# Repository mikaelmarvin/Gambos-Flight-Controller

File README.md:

# Gambos flight controller

Custom **STM32F446** flight-controller PCB and firmware — schematic through layout, manufacture, assembly, bring-up, application and driver development.

## At a glance

|               |                                                                        |
| ---------------| ------------------------------------------------------------------------|
| **MCU**       | STM32F446RET6 (Cortex-M4 + FPU)                                        |
| **Sensors**   | Accelerometer, gyroscope, magnetometer, barometer, temperature         |
| **Storage**   | External flash + microSD                                               |
| **Actuation** | 5× hobby servo PWM, ESC motor PWM                                      |
| **Wireless**  | nRF24L01+ telemetry / command link                                     |
| **Debug**     | SWD + UART (SEGGER J-Link)                                             |
| **PCB**       | 4-layer, 75 × 50 mm — KiCad, manufactured **v1.0**                     |
| **Firmware**  | CMake, FreeRTOS — `gambos` target                                  |
| **Status**    | v1.0 built; hardware bring-up in progress; flight software in progress |
| **Schematic** | [Gambos PCB schematic (PDF)](https://github.com/mikaelmarvin/gambos_hardware/blob/main/docs/gambos-pcb.pdf) — KiCad export, v1.0 |

## Schematic (v1.0)

The full board schematic is published as a PDF:

**[Gambos PCB schematic (PDF)](https://github.com/mikaelmarvin/gambos_hardware/blob/main/docs/gambos-pcb.pdf)**

The KiCad design, the schematic PDF and the hardware documentation live in a separate repository, [gambos_hardware](https://github.com/mikaelmarvin/gambos_hardware).

## Render and Bring-up setup

<p align="center">
  <table cellspacing="0" cellpadding="12">
    <tr>
      <td align="center" valign="top">
        
        <br>
        <sub>3D PCB render</sub>
      </td>
      <td align="center" valign="top">
        
        <br>
        <sub>Testing the power section on the bench</sub>
      </td>
    </tr>
  </table>
</p>

Render of v1.0 layout in KiCad (left) and early bench bring-up (right), started with the power section before moving to testing other peripherals.

## Hardware block diagram

<p align="center">
  
  <br>
  <sub>Hardware block diagram</sub>
</p>

Buses, actuation, and interfaces are described in [Hardware architecture](https://github.com/mikaelmarvin/gambos_hardware/blob/main/docs/hardware-architecture.md).

## Software architecture

*(diagram pending)* — layer stack, drivers, RTOS tasks, and flight logic are described in [Software architecture](docs/software/software-architecture.md).

## Documentation

Full index: **[docs/index.md](docs/index.md)**

**Hardware:** documentation for the v1.0 board lives in [gambos_hardware](https://github.com/mikaelmarvin/gambos_hardware#documentation-v10) — architecture, physical design, power, storage, sensing, user interface, and the hardware roadmap.

**Software:** [docs/software/software-architecture.md](docs/software/software-architecture.md) → [project/README.md](project/README.md) · [Firmware roadmap](docs/software/roadmap.md)

## Repository layout

| Directory                | Purpose                                         |
| ------------------------ | ----------------------------------------------- |
| `[project/](project/)`   | STM32 firmware (CMake, FreeRTOS)                |
| `[docs/](docs/)`         | Software documentation, figures                 |

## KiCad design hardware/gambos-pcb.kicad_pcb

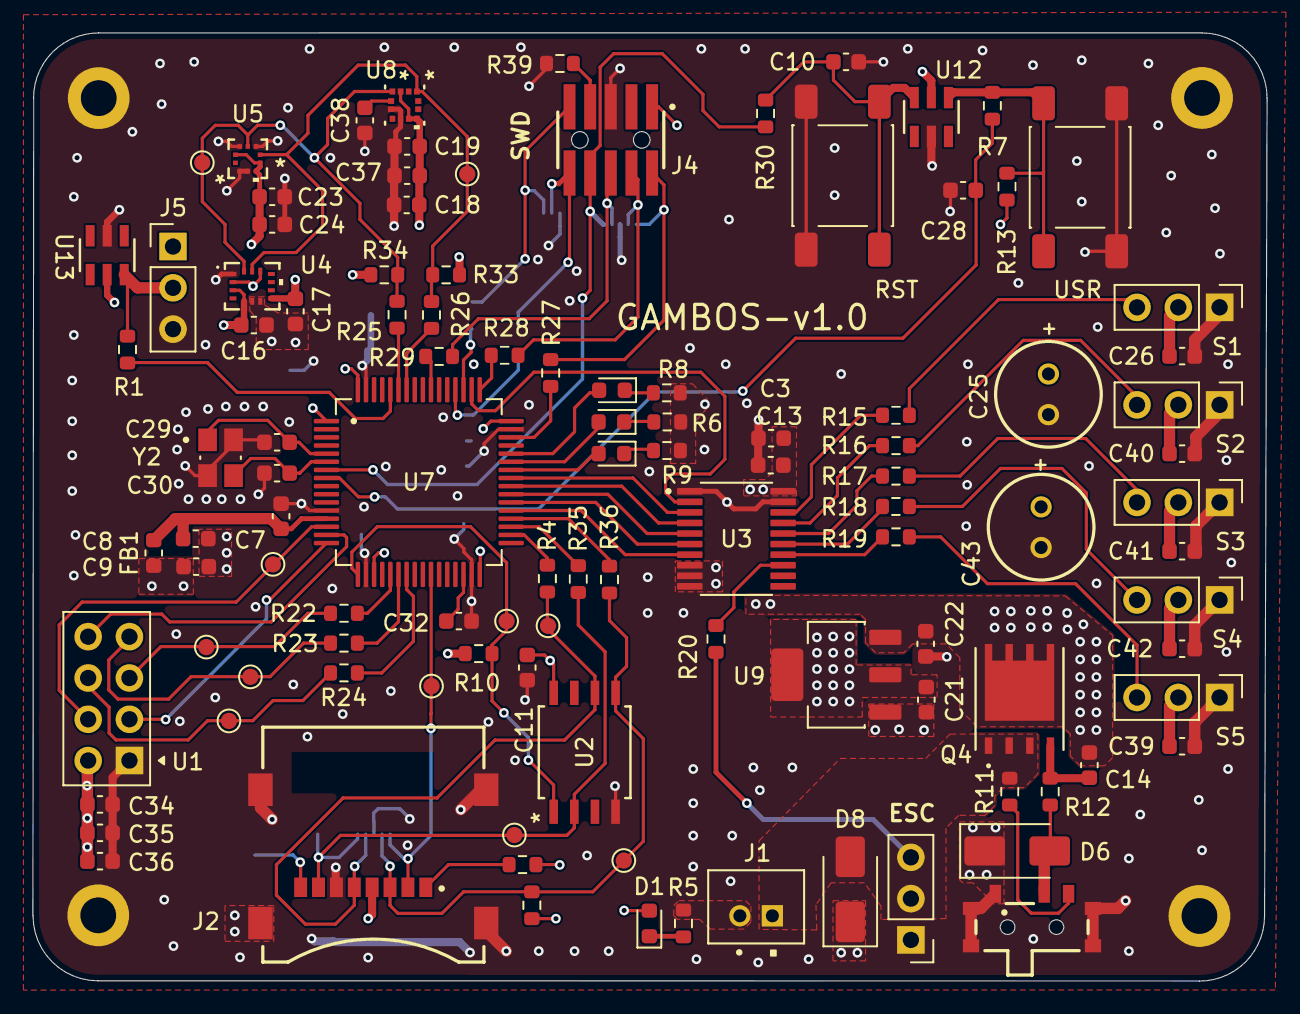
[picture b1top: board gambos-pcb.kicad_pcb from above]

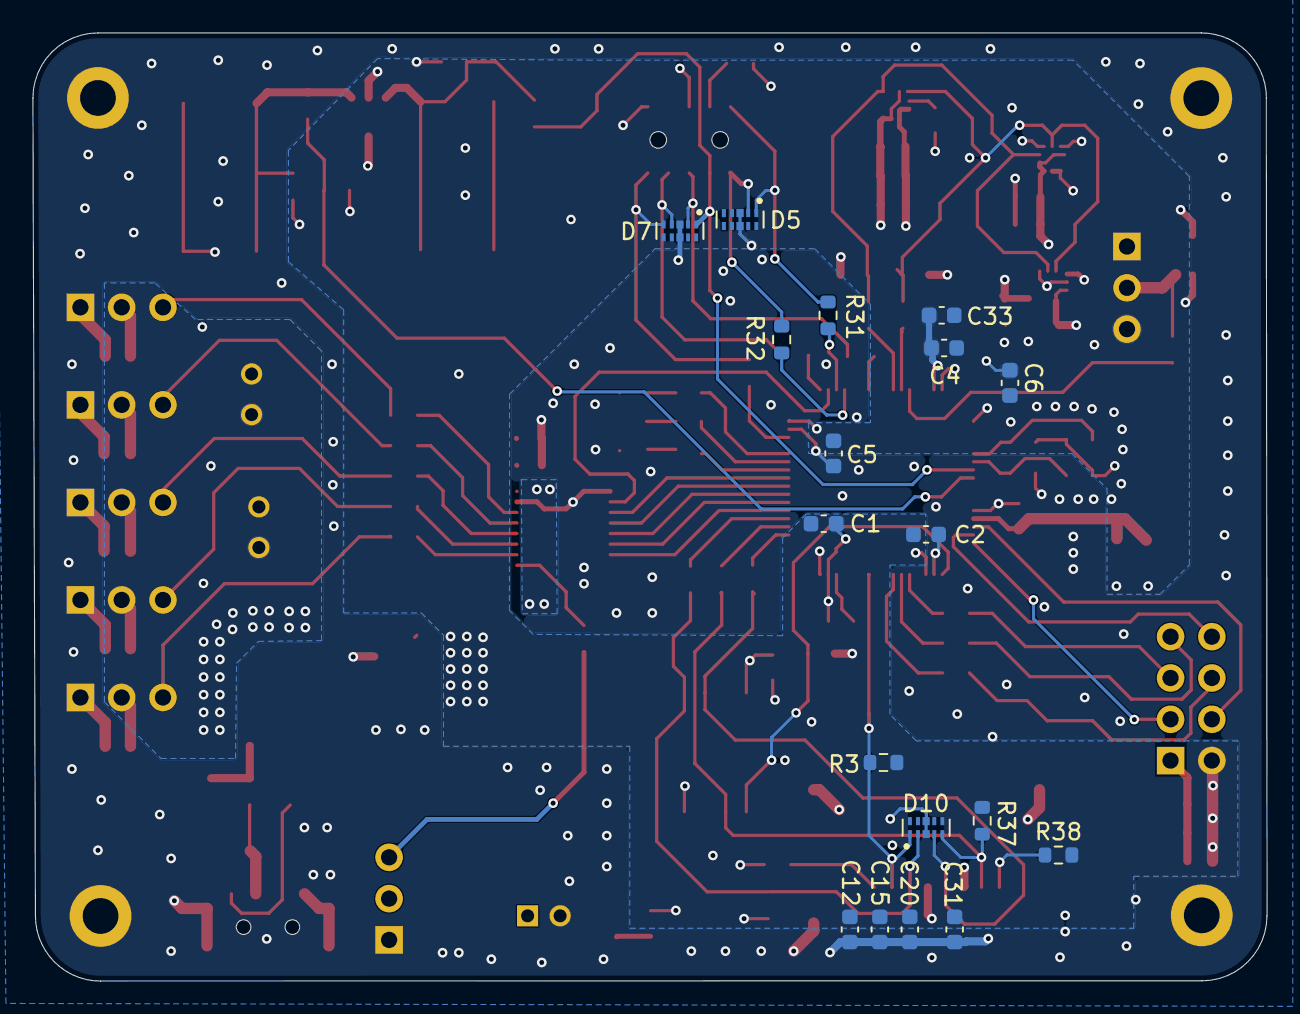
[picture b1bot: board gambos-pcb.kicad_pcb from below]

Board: 4 copper layers, 75.9 x 58.3 mm, 130 parts (18 on the bottom side), 77 nets.

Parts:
C1, C2, C4, C5, C10, C11, C13, C14, C16, C17, C19, C23, C24, C28, C31, C33, C35, C37: 100n; C_0603_1608Metric
C3, C8, C9, C20, C22: 1u; C_0603_1608Metric
C6, C15, C18, C26, C36, C39, C40, C41, C42: 10u; C_0603_1608Metric
C7, C34: 10n; C_0603_1608Metric
C12: 22u; C_0603_1608Metric
C21, C32: 4u7; C_0603_1608Metric
C25, C43: 470u; WCAP-ATG8_6.3X11_DXL_
C29, C30: 8p; C_0603_1608Metric
C38: 220n; C_0603_1608Metric
D1: LED0; LED_0603_1608Metric
D2: LED1; LED_0603_1608Metric
D3: LED2; LED_0603_1608Metric
D4: LED3; LED_0603_1608Metric
D5, D7, D10: ESD8104MUTAG; DIO_ESD8104MUTAG
D6, D8: SMAJ5.0CA; D_SMA
FB1: 120R; L_0603_1608Metric
H1, H2, H3, H4: MountingHole_Pad; MountingHole_2.2mm_M2_DIN965_Pad
J1: JST-PH
J2: Micro_SD_Card; GCT_MEM2067-02-180-00-A_REVB
J4: FTSH-105-01-F-DV-K-A; SAMTEC_FTSH-105-01-F-DV-K-A
J5, J7, J9, J10, J11, J12, J13: Conn_01x03_Pin; PinHeader_1x03_P2.54mm_Vertical
Q4: DMP3010LPSQ-13
R1, R10, R12, R13: 10k; R_0603_1608Metric
R2, R3, R7, R21, R37, R38: 47k; R_0603_1608Metric
R4, R15, R16, R17, R18, R19, R20, R22, R23, R24, R25, R26, R27, R28, R29, R31, R32, R35, R36: 0R; R_0603_1608Metric
R5, R6, R8, R9: 260R; R_0603_1608Metric
R11: 100k; R_0603_1608Metric
R30: 470R; R_0603_1608Metric
R33, R34: 4k7; R_0603_1608Metric
R39: 100R; R_0603_1608Metric
SW1, SW3: SW_Push; SW_Push_1P1T_NO_E-Switch_TL3301NxxxxxG
Slide_SW1: 450404015514
TP2, TP3, TP4, TP5, TP6, TP7, TP8, TP9, TP12, TP13, TP14: TestPoint; TestPoint_Pad_D1.0mm
U1: NRF24L01_Breakout; nRF24L01_Breakout
U2: AT25SF128A-SHB-T; IC8_AT25SF128A-SHB-T_ADO
U3: SN74AHCT541PWR; SOP65P640X120-20N
U4: LSM6DSVTR
U5: BMP384; LGA10_2.0X2.0X0.95_BOS
U7: STM32F446RET6
U8: IIS2MDCTR; LGA-12_2X2X0P7_STM
U9: LDL1117S33R
U12, U13: CM1293A-04SO; SC74-6_3P1X1P7_ONS
Y2: TSX-3225_26MHZ; XTAL_TSX-3225_26.0000MF09Z-AC0

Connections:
+3.3VA: C7.1, C8.1, FB1.1, U7.13 (VDDA)
+3V3: C1.1, C2.1, C4.1, C5.1, C6.1, C9.1, C11.1, C12.2, C15.2, C16.1, C17.1, C18.1, C19.1, C20.2, C21.1, C23.1, C24.2, C31.2, C33.1, C34.1, C35.1, C36.1, C37.1, D1.2 (A), FB1.2, J2.4 (VDD), J4.01, J5.1, R2.1, R3.1, R10.1, R13.2, R21.1, R33.1, R34.1, R37.1, R38.2, U1.2 (VCC), U2.8 (VCC), U4.2 (SDX), U4.3 (SCX), U4.5 (VDD_IO), U4.8 (VDD), U4.12 (CS), U5.1 (VDDIO), U5.6 (CSB), U5.10 (VDD), U7.1 (VBAT), U7.19 (VDD), U7.32 (VDD), U7.48 (VDD), U7.64 (VDD), U8.3 (CS), U8.9 (VDD), U8.10 (VDD_IO), U9.2 (VOUT_2), U9.4 (VOUT_1), U12.5 (VP), U13.5 (VP)
+5V: C3.1, C13.1, C14.1, C22.1, C25.1, C26.1, C39.1, C40.1, C41.1, C42.1, C43.1, J7.2, J9.2, J10.2, J11.2, J12.2, Q4.5 (D), Q4.6 (D), Q4.7 (D), Q4.8 (D), U3.20 (VCC), U9.3 (VIN)
/Schematic/I2C.SCL: R26.2, R33.2, TP12.1 (1_1), U4.13 (SCL), U5.2 (SCK), U8.1 (SCL/SPC)
/Schematic/I2C.SDA: R25.2, R34.2, TP13.1 (1_1), U4.14 (SDA), U5.4 (SDI), U8.4 (SDA/SDI/SDO)
/Schematic/Microcontroller/BOOT0: R1.2, U7.60 (BOOT0)
/Schematic/Microcontroller/BOOT0_ESD: J5.2, R1.1, U13.6 (CH4)
/Schematic/Microcontroller/HSE_IN: C29.2, U7.5 (PH0), Y2.1
/Schematic/Microcontroller/HSE_OUT: C30.1, U7.6 (PH1), Y2.3
/Schematic/Microcontroller/NRST_ESD: C10.1, R30.1, SW3.2, U12.6 (CH4)
/Schematic/Microcontroller/PWMs.ESC_IN: U3.7 (A6), U7.37 (PC6)
/Schematic/Microcontroller/PWMs.SERVO1_IN: U3.2 (A1), U7.50 (PA15)
/Schematic/Microcontroller/PWMs.SERVO2_IN: U3.3 (A2), U7.41 (PA8)
/Schematic/Microcontroller/PWMs.SERVO3_IN: U3.4 (A3), U7.40 (PC9)
/Schematic/Microcontroller/PWMs.SERVO4_IN: U3.5 (A4), U7.39 (PC8)
/Schematic/Microcontroller/PWMs.SERVO5_IN: U3.6 (A5), U7.38 (PC7)
/Schematic/Microcontroller/USER_BTN: C28.1, R7.2, U7.8 (PC0)
/Schematic/Microcontroller/USER_BTN_ESD: R7.1, R13.1, SW1.2, U12.4 (CH3)
/Schematic/Microcontroller/USER_LED1: D2.2 (A), U7.44 (PA11)
/Schematic/Microcontroller/USER_LED2: D3.2 (A), U7.43 (PA10)
/Schematic/Microcontroller/USER_LED3: D4.2 (A), U7.42 (PA9)
/Schematic/Power and ESC/GATE: C14.2, Q4.4 (G), R12.2
/Schematic/Power and ESC/GATE_CTRL: D6.2 (A2), R12.1, Slide_SW1.2
/Schematic/Power and ESC/OFF: R11.2, Slide_SW1.3
/Schematic/Power and ESC/V_IN: D8.2 (A2), J1.1 (V_BAT), J13.2, Q4.1 (S), Q4.2 (S), Q4.3 (S), R11.1
/Schematic/SPI1.MISO_1: R23.2, TP4.1 (1_1), U1.7 (MISO)
/Schematic/SPI1.MOSI_1: R24.2, TP5.1 (1_1), U1.6 (MOSI)
/Schematic/SPI1.SCK_1: R22.2, TP3.1 (1_1), U1.5 (SCK)
/Schematic/SPI2.MISO_2: D10.5, J2.7 (DAT0), R35.2, R37.2, TP7.1 (1_1), U2.2 (SO(I/O1))
/Schematic/SPI2.MOSI_2: D10.2, J2.3 (CMD), R2.2, R36.2, TP14.1 (1_1), U2.5 (SI(I/O0))
/Schematic/SPI2.SCK_2: D10.4, J2.5 (CLK), R4.2, TP6.1 (1_1), U2.6 (SCK)
/Schematic/Servos and connectors/ESC_OUT: J13.3, R20.2
/Schematic/Servos and connectors/PWM1_1_5V: R16.1, U3.17 (Y2)
/Schematic/Servos and connectors/PWM2_1_5V: R15.1, U3.18 (Y1)
/Schematic/Servos and connectors/PWM3_1_5V: R19.1, U3.14 (Y5)
/Schematic/Servos and connectors/PWM3_2_5V: R20.1, U3.13 (Y6)
/Schematic/Servos and connectors/PWM3_3_5V: R18.1, U3.15 (Y4)
/Schematic/Servos and connectors/PWM3_4_5V: R17.1, U3.16 (Y3)
/Schematic/Servos and connectors/SERVO1_OUT: J10.3, R15.2
/Schematic/Servos and connectors/SERVO2_OUT: J7.3, R16.2
/Schematic/Servos and connectors/SERVO3_OUT: J9.3, R17.2
/Schematic/Servos and connectors/SERVO4_OUT: J11.3, R18.2
/Schematic/Servos and connectors/SERVO5_OUT: J12.3, R19.2
FLASH_CS: R10.2, TP9.1 (1_1), U2.1 (*CS), U7.17 (PA3)
GND: C1.2, C2.2, C3.2, C4.2, C5.2, C6.2, C7.2, C8.2, C9.2, C10.2, C11.2, C12.1, C13.2, C15.1, C16.2, C17.2, C18.2, C19.2, C20.1, C21.2, C22.2, C23.2, C24.1, C25.2, C26.2, C28.2, C29.1, C30.2, C31.1, C32.2, C33.2, C34.2, C35.2, C36.2, C37.2, C38.2, C39.2, C40.2, C41.2, C42.2, C43.2, D5.3 (GND), D5.8 (GND), D6.1 (A1), D7.3 (GND), D7.8 (GND), D8.1 (A1), D10.3 (GND), D10.8 (GND), H1.1 (1_1), H2.1 (1_1), H3.1 (1_1), H4.1 (1_1), J1.2 (GND), J2.6 (VSS), J2.9, J2.10, J2.11, J2.12, J4.05, J5.3, J7.1, J9.1, J10.1, J11.1, J12.1, J13.1, R5.2, R6.1, R8.1, R9.1, R39.1, SW1.1, SW3.1, Slide_SW1.1, Slide_SW1.Z1, Slide_SW1.Z2, Slide_SW1.Z3, Slide_SW1.Z4, U1.1 (GND), U2.4 (GND), U3.1 (~OE1), U3.8 (A7), U3.9 (A8), U3.10 (GND), U3.19 (~OE2), U4.1 (SDO/SA0), U4.6 (GND), U4.7 (GND), U5.3 (VSS), U5.5 (SDO), U5.8 (VSS), U5.9 (VSS), U7.12 (VSSA), U7.18 (VSS), U7.31 (VSS), U7.47 (VSS), U7.63 (VSS), U8.6 (GND), U8.8 (GND), U9.1 (GND), U12.2 (VN), U13.2 (VN), Y2.2 (GND), Y2.4 (GND)
IRQ_SLD: U1.8 (IRQ), U7.15 (PA1)
NRF24_CE_SLD: U1.3 (CE), U7.16 (PA2)
NRF24_CS_SLD: TP2.1 (1_1), U1.4 (~CSN), U7.14 (PA0)
NRST: D7.1, J4.08, R30.2, U7.7 (NRST)
unnamed: D1.1 (K), R5.1
unnamed: D2.1 (K), R8.2
unnamed: D3.1 (K), R6.2
unnamed: D4.1 (K), R9.2
unnamed: J2.8 (DAT1), R38.1
unnamed: J2.1 (DAT2), R21.2
unnamed: J4.07, R39.2
unnamed: R22.1, U7.21 (PA5)
unnamed: R23.1, U7.22 (PA6)
unnamed: R24.1, U7.23 (PA7)
unnamed: R27.1, U7.46 (PA13)
unnamed: R28.1, U7.49 (PA14)
unnamed: R29.1, U7.55 (PB3)
unnamed: R26.1, U7.58 (PB6)
unnamed: R25.1, U7.59 (PB7)
unnamed: R4.1, U7.34 (PB13)
unnamed: R35.1, U7.35 (PB14)
unnamed: R36.1, U7.36 (PB15)
unnamed: R31.2, U7.51 (PC10)
unnamed: R32.2, U7.52 (PC11)
unnamed: C32.1, U7.30 (VCAP_1)
unnamed: C38.1, U8.5 (C1)
SD_CS: D10.1, J2.2 (DAT3/CD), R3.2, TP8.1 (1_1), U7.26 (PB0)
SWCLK: D7.4, J4.04, R28.2
SWDIO: D7.5, J4.02, R27.2
SWO: D7.2, J4.06, R29.2
UART4_RX: D5.2, J4.10, R32.1
UART4_TX: D5.1, J4.09, R31.1

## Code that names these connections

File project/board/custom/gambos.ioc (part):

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Mcu.Name=STM32F446R(C-E)Tx
Mcu.Package=LQFP64
Mcu.UserName=STM32F446RETx
PA0-WKUP.GPIOParameters=GPIO_Label
PA0-WKUP.GPIO_Label=RF_IRQ
PA0-WKUP.Signal=GPXTI0
PA1.GPIOParameters=GPIO_Label
PA1.GPIO_Label=RF_CS
PA1.Signal=GPIO_Output
PA10.GPIOParameters=GPIO_Label
PA10.GPIO_Label=LED2
PA10.Signal=GPIO_Output
PA11.GPIOParameters=GPIO_Label
PA11.GPIO_Label=LED1
PA11.Signal=GPIO_Output
PA12.GPIOParameters=GPIO_Label
PA12.GPIO_Label=BUFF_EN
PA12.Signal=GPIO_Output
PA13.Mode=Trace_Asynchronous_SW
PA13.Signal=SYS_JTMS-SWDIO
PA14.Mode=Trace_Asynchronous_SW
PA14.Signal=SYS_JTCK-SWCLK
PA15.GPIOParameters=GPIO_Label
PA15.GPIO_Label=SERVO1
PA15.Signal=S_TIM2_CH1_ETR
PA2.GPIOParameters=GPIO_Label
PA2.GPIO_Label=RF_CE
PA2.Signal=GPXTI2
PA3.GPIOParameters=GPIO_Label
PA3.GPIO_Label=FLASH_CS
PA3.Signal=GPIO_Output
PA5.Mode=Full_Duplex_Master
PA5.Signal=SPI1_SCK
PA6.Mode=Full_Duplex_Master
PA6.Signal=SPI1_MISO
PA7.Mode=Full_Duplex_Master
PA7.Signal=SPI1_MOSI
PA8.GPIOParameters=GPIO_Label
PA8.GPIO_Label=SERVO2
PA8.Signal=S_TIM1_CH1
PA9.GPIOParameters=GPIO_Label
PA9.GPIO_Label=LED3
PA9.Signal=GPIO_Output
PB13.Mode=Full_Duplex_Master
PB13.Signal=SPI2_SCK
PB14.Mode=Full_Duplex_Master
PB14.Signal=SPI2_MISO
PB15.Mode=Full_Duplex_Master
PB15.Signal=SPI2_MOSI
PB3.Mode=Trace_Asynchronous_SW
PB3.Signal=SYS_JTDO-SWO
PB6.Mode=I2C
PB6.Signal=I2C1_SCL
PB7.Mode=I2C
PB7.Signal=I2C1_SDA
PC0.GPIOParameters=GPIO_Label
PC0.GPIO_Label=USER_BTN
PC0.Signal=GPIO_Input
PC10.Mode=Asynchronous
PC10.Signal=UART4_TX
PC11.Mode=Asynchronous
PC11.Signal=UART4_RX
PC6.GPIOParameters=GPIO_Label
PC6.GPIO_Label=ESC
PC6.Signal=S_TIM3_CH1
PC7.GPIOParameters=GPIO_Label
PC7.GPIO_Label=SERVO5
PC7.Signal=S_TIM3_CH2
PC8.GPIOParameters=GPIO_Label
PC8.GPIO_Label=SERVO4
PC8.Signal=S_TIM3_CH3
PC9.GPIOParameters=GPIO_Label
PC9.GPIO_Label=SERVO3
PC9.Signal=S_TIM3_CH4
PH0-OSC_IN.Mode=HSE-External-Oscillator
PH0-OSC_IN.Signal=RCC_OSC_IN
PH1-OSC_OUT.Mode=HSE-External-Oscillator
PH1-OSC_OUT.Signal=RCC_OSC_OUT
RCC.HSE_VALUE=26000000
RCC.SYSCLKFreq_VALUE=180000000
RCC.SYSCLKSource=RCC_SYSCLKSOURCE_PLLCLK
board=custom

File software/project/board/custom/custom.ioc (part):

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Mcu.Name=STM32F446R(C-E)Tx
Mcu.Package=LQFP64
Mcu.UserName=STM32F446RETx
PA0-WKUP.GPIOParameters=GPIO_Label
PA0-WKUP.GPIO_Label=NRF24_CS
PA0-WKUP.Signal=GPIO_Output
PA1.GPIOParameters=GPIO_Label
PA1.GPIO_Label=IRQ
PA1.Signal=GPXTI1
PA10.GPIOParameters=GPIO_Label
PA10.GPIO_Label=LED2
PA10.Signal=GPIO_Output
PA11.GPIOParameters=GPIO_Label
PA11.GPIO_Label=LED1
PA11.Signal=GPIO_Output
PA13.Mode=Trace_Asynchronous_SW
PA13.Signal=SYS_JTMS-SWDIO
PA14.Mode=Trace_Asynchronous_SW
PA14.Signal=SYS_JTCK-SWCLK
PA15.GPIOParameters=GPIO_Label
PA15.GPIO_Label=S1
PA15.Signal=S_TIM2_CH1_ETR
PA2.GPIOParameters=GPIO_Label
PA2.GPIO_Label=NRF24_CE
PA2.Signal=GPIO_Output
PA3.GPIOParameters=GPIO_Label
PA3.GPIO_Label=FLASH_CS
PA3.Signal=GPIO_Output
PA5.Mode=Full_Duplex_Master
PA5.Signal=SPI1_SCK
PA6.Mode=Full_Duplex_Master
PA6.Signal=SPI1_MISO
PA7.Mode=Full_Duplex_Master
PA7.Signal=SPI1_MOSI
PA9.GPIOParameters=GPIO_Label
PA9.GPIO_Label=LED3
PA9.Signal=GPIO_Output
PB0.GPIOParameters=GPIO_Label
PB0.GPIO_Label=SD_CS
PB0.Signal=GPIO_Output
PB13.Mode=Full_Duplex_Master
PB13.Signal=SPI2_SCK
PB14.Mode=Full_Duplex_Master
PB14.Signal=SPI2_MISO
PB15.Mode=Full_Duplex_Master
PB15.Signal=SPI2_MOSI
PB3.Mode=Trace_Asynchronous_SW
PB3.Signal=SYS_JTDO-SWO
PB6.Mode=I2C
PB6.Signal=I2C1_SCL
PB7.Mode=I2C
PB7.Signal=I2C1_SDA
PC0.GPIOParameters=GPIO_Label
PC0.GPIO_Label=USR_BTN
PC0.Signal=GPIO_Input
PC10.Mode=Asynchronous
PC10.Signal=UART4_TX
PC11.Mode=Asynchronous
PC11.Signal=UART4_RX
PC6.GPIOParameters=GPIO_Label
PC6.GPIO_Label=ESC_PWM
PC6.Signal=S_TIM3_CH1
PC7.GPIOParameters=GPIO_Label
PC7.GPIO_Label=S5
PC7.Signal=S_TIM3_CH2
PC8.GPIOParameters=GPIO_Label
PC8.GPIO_Label=S4
PC8.Signal=S_TIM3_CH3
PC9.GPIOParameters=GPIO_Label
PC9.GPIO_Label=S3
PC9.Signal=S_TIM3_CH4
PH0-OSC_IN.Mode=HSE-External-Oscillator
PH0-OSC_IN.Signal=RCC_OSC_IN
PH1-OSC_OUT.Mode=HSE-External-Oscillator
PH1-OSC_OUT.Signal=RCC_OSC_OUT
RCC.HSE_VALUE=26000000
RCC.SYSCLKFreq_VALUE=180000000
RCC.SYSCLKSource=RCC_SYSCLKSOURCE_PLLCLK
board=custom

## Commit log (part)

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2026-02-28 Project setup
2026-02-28 Removed unnecessary autogenerated comments from main.c
2026-02-28 Removed some more unnecessary comments from i2c.c and deleted the unnecessary Release build preset
2026-03-03 Added initialization code for devkit and custom pcb to the project, now it is possible to build both
2026-03-21 must save this
2026-03-30 Flashed the bluepill first time
2026-04-04 fix: fix
2026-04-06 Initialization function fro nrf24 done
2026-04-07 Added timestamp with logs
2026-04-10 C++ is online
2026-04-10 Clean repo
2026-04-10 Fixes
2026-04-13 Flashed something useful, messaging, button handler and tested subscribing
2026-04-13 flashed, tried messaging, button handler ...
2026-04-14 Separated app code from generated code
2026-04-17 small steps
2026-04-17 small step
2026-04-24 fix: restructured repo for hardware integration
2026-04-25 New structure of the repository
2026-04-25 New repository structure with hardware and software part
2026-04-26 Added new hardware files
2026-04-26 Added project landing page
2026-05-11 Restructuring also
2026-05-11 Docker environment fixes
2026-05-12 LEDs work
2026-05-12 LEDs work again
2026-05-12 Some changes
2026-05-12 Flashing building cleaning
2026-05-12 Added debugging session ability
2026-05-12 Fixed button, disabled its pull-up
2026-05-18 Added partial documentation about the project
2026-05-19 Adjusted flashing firmware to the custom board to use only JLinkExe, no opencd fallback, simpler code and documentation
2026-05-20 Ignore KiCad lock files (~*.lck)
2026-05-20 Added photo of the pcb during bring-up
2026-05-21 Better structuring of the docs
2026-05-22 First respectable iteration of a good documentation
2026-05-22 Fixed the Future-improvements page and changed it for the roadmap page
2026-05-25 A lot was done, not just documentation
2026-05-25 Better block diagram picture
2026-05-25 Added pdf file of the KiCad schematic
2026-05-25 Fixed small typo in docs
2026-05-29 Added the DelayableWork class
2026-05-30 Delayable work items tested and working
2026-06-02 Tested flash, pwm, i2c
2026-06-08 Added LittleFS source code to the build
2026-06-16 LittleFS integration and flash driver
2026-06-22 Changes for i2c and spi synchronization
2026-06-22 new structure for all handlers
2026-06-23 minor changes
2026-06-28 Done with storage, must test now
2026-06-28 Fixed clangd issues
2026-06-28 Fixed clangd issues again
2026-06-30 Storage handler and littleFS working as expected
2026-06-30 Initial commit for pwm handler
